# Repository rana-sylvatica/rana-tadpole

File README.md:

# rana-tadpole
## Pocket-sized digital controller

### Overview:

#### NOTE: I am in the process of updating this repository with information and design files for the Rana Tadpole V2.  This process isn't quite done yet - wait a few days if you are looking to build your own Tadpole V2 (I'll remove this note once I'm done with the update).  The V2 motherboard files are now up, I'll be getting to adding the case file and other stuff Soon(TM)

The Rana Tadpole is a pocket-sized 20-button digital controller, designed for platform fighters but usable for other fighting games, platformers, etc.

Unlike most other similar controller designs that use either keyboard switches or arcade buttons, the Tadpole uses mouse switches (Kailh GM 4.0 if using the provided BOM files - there are other compatible switches that can be subsituted as well at the builders discretion).

With the mouseclick switches, the Tadpole has best-in-class button travel distance, a mere 0.8mm until bottom-out, for fast reactions and precise inputs.  The mouseclick switches also enable the entire board to be easily factory assembled, cutting down on cost and build time.

This repository contains design files for all required components to build your own Rana Tadpole.  Scroll down for open source license information, parts list, link to build guide, and user guide.

### Attributions:

Many thanks to [Quark](https://github.com/Armastardo) for the PCB design for both the motherboard and daughterboard!

### Licensing:

This project is licensed under CERN Open Hardware Licence Version 2 - Strongly Reciprocal

In short, this means:
 - License applies to publicly available hardware designs
 - Allows use, reproduction, modification, distribution, and sale of the design
 - License requires distribution under same terms, attribution to original designer(s)
 - Does not grant trademark rights, includes disclaimer of liability
 - License may be terminated for non-compliance

Anyone may use these design files to make their own Rana Tadpole(s) for personal use or to sell, or modify the design however they wish.
However, if a modified design is distributed (either digitally or physically beyond personal use), the modified design must be publicly posted under the same terms.

Note: if selling Rana Tadpoles, YOU MUST link to this repo (or your fork of this repo, if you modify the design) on your store page.  If selling in-person, MAKE SURE to communicate that this is an open-source project, and provide (via QR code or similar) a way for the customer to access this repo (or the applicable fork).

All these files are posted as-is. This source is distributed WITHOUT ANY EXPRESS OR IMPLIED WARRANTY, INCLUDING OF MERCHANTABILITY, SATISFACTORY QUALITY AND FITNESS FOR A PARTICULAR PURPOSE. 

If you are interested in supporting this project, donations are accepted at [paypal.me/RanaLabs](https://www.paypal.me/RanaLabs).

### Rana Tadpole V2 Animation

https://github.com/user-attachments/assets/85642930-a598-4af2-86c9-3ccd63989db8

### Parts list:

The Rana Tadpole build requires the following list of components:
 - #### Case
   - 3D printed or CNC machined, see CAD files
   - Additional notes:
     - JLCPCB or PCBway are affordable CNC machining vendors.  If you want the screw holes threaded at the factory (rather than doing it by hand), you will need to create a drawing specifying the thread type, hole position, and thread depth.
     - If 3D printing the case, the provided file is designed to have the screws thread directly into the plastic.  Getting a good fit on your printer may require some adjustment.  The files can also be modified to accept heat set inserts, or other screws (such as specialized thread-cutting screws) can be subsituted for the machine screws as well.  Just do your research on hole diameters, etc.
     - I plan to post a case model in the future that is designed for ordering inexpensively from a 3D printing service such as JLCPCB, but that design is not quite ready yet.
 - #### Button caps
   - These can be purchased from me (injection molded PBT) or 3D printed.  Link to purchase: https://ko-fi.com/s/469357a31c
   - Additional notes for 3D printing:
     - For best quality, order the Tadpole_Button_x8 file from JLCPCB or other 3D printing service in SLS or MJF nylon
     - Resin printing also works well
     - These buttons are difficult to print with a FDM printer, but please let me know if you find a modification to the design that allows them to print well!
 - #### Motherboard
   - Embedded rp2040 PCB with factory-soldered mouseclick switches, see KiCAD and Gerber files
   - The Gerber and assembly files are generated for ordering through JLCPCB.  Other PCB fabs can also be used, but you may need to generate the production files differently.  (applicable to all three PCB components here)
 - #### USB Breakout board
   - USB C board with case grounding and ESD protection, see KiCAD and Gerber files
 - #### Backplate
   - Silkscreen PCB (or lasercut/3D printed). KiCAD/Gerber, DXF, and .STEP files available
 - #### Foam pads
   - These can be purchased from me (die cut textured silicone rubber), or lasercut from EVA foam or similar.  Link to purcahse from me: https://ko-fi.com/s/3146277fc0
   - Example foam that works well: https://www.amazon.com/gp/product/B07V5PR459
 - ####  Ribbon cable
   - 12 pin, 0.5mm pitch, 50mm length FFC, Same side contacts (sometimes called "Forward Direction"
   - Example items: https://www.digikey.com/en/products/detail/assmann-wsw-components/AFFC-050-12-051-11/6570261, [https://www.aliexpress.us/item/3256803954097404.html](https://www.aliexpress.us/item/3256805295157150.html)
 - #### Grounding foam
   - Optional, but helps with ESD protection if using the PCB backplate.  Link: https://www.aliexpress.us/item/3256805239781097.html 
 - #### Hardware
   - Screws
     - 2x M3x6mm (for securing the USB C board).  Link: https://www.mcmaster.com/94500A221/
     - 6x M3x10mm (for securing the backplate/motherboard).  Link: [https://www.mcmaster.com/92095A181/](https://www.mcmaster.com/92095A182/) OR [https://www.aliexpress.us/item/2255800885711092.html](https://www.aliexpress.us/item/3256804883804669.html?)
   - Spacers
     - Can either use:
       - 6x X-profile o-rings, dash number 104.  Link: https://www.mcmaster.com/90025K513/
       - 3mm thick gaskets using the files in this repo - these can be 3D printed in soft TPU or die cut from silicone or similar

#### Extras: 
 - #### USB C-USB A cable (for PC/switch compatibility)
   - Any USB data cable will work
 - #### USB C-GCC cable (for gamecube/wii compatibility)
   - Several suppliers, but HHL or my store are good options: https://handheldlegend.com/products/retro-c-gamecube-cable-usb-c-to-gamecube-cable?variant=40183052337286, https://ko-fi.com/s/bc4af1084a
 - #### Belt clip
   - .STL file provided for 3D printing
 - #### Carry bag
   - Canvas zipper pouches that measure at least 8" x 6" work well

### Assembly guide:

See YouTube video: https://www.youtube.com/watch?v=oF4wL67agoM

NOTE: This is slightly out of date now, given the V2 version that adds the slide switch.  I may eventually make an updated build guide, but for now this is still mostly relevant.

### Dual Firmware Switch:

The Rana Tadpole V2 has a fun new feature - two different flash memory chips, with a switch on the side of the controller to select between them.  This is very useful if you want to use your Tadpole for both platform fighters and traditional fighters - you can load HayBox on one memory slot and GP2040-CE on the other.

#### IMPORTANT NOTE: Do not flip the firmware switch while the device is plugged in.  Unplug it, flip the switch to the other position, and plug it back in.

### Aux USB C Port:

Another new feature of the Tadpole V2 is the auxillary USB C port on the side of the controller.  The main purpose of this is for passthrough authentication when using GP2040-CE firmware, to get PS4/PS5 compatibility without additional input latency (see image below).

This port is also capable of becoming a flexible expansion port in the future, with many possibilities including: an adapter to connect a GCC for mixed input (left hand GCC, right hand Tadpole) gameplay, pluggable analog joystick(s), etc.

#### MORE INFO TO COME HERE

### Firmwares:

There are three different open-source firmwares that the Rana Tadpole is compatible with: 
 - [HayBox](https://github.com/JonnyHaystack/HayBox)
   - Compatible with:
     - PC (as XInput or DInput device)
     - GameCube
     - Wii
     - Switch
     - N64
     - Other consoles (via Brook Wingman adapter)
 - [pico-rectangle](https://github.com/JulienBernard3383279/pico-rectangle)
   - Compatible with:
     - PC (as emulated GC adapter or XInput device)
     - GameCube
     - Wii
     - Switch
     - Other consoles (via Brook Wingman adapter)
 - [GP2040-CE](https://gp2040-ce.info/#/README)
   - Generally used for traditional fighting games, compatible with:
     - PC
     - PS3
     - PS4
     - Switch
     - Other consoles (via Brook Wingman adapter)
    
    Please refer to the documentation for each firmware for more information.

   #### Default layouts:

   HayBox and pico-rectangle:

   GP2040-CE:

   #### Switching and flashing firmwares:

   To flash a firmware, the rp2040 chip inside the Tadpole motherboard must be put in BOOTSEL mode, at which point the controller will show up as a mass storage device when plugged into a computer and the fimrware file can be copied to it.

   There are two ways of putting the Tadpole in BOOTSEL mode.  First, there is a small button on the motherboard that can be held down as the board is plugged into the PC.  However, this can be inconvenient as it requires disassembling the controller to access this button.

   The alternative method is to use hold a button (or button combination) specific to the particular firmware, when plugging into the PC.
   - For HayBox: hold Start (may be different if using a fork of HayBox.  For example, https://github.com/GRAMCTRL/HayBox-GRAM uses "A" as the button hold to get into BOOTSEL mode).
   - For pico-rectangle: hold C-Right
   - For GP2040-CE: hold Start + Select + Up (refer to the GP2040-CE layout graphic)
  
   Additional notes on HayBox:
   - The HayBox-GRAM fork brings a few features such as web remapping (see below) and a dedicated Rivals 2 mode, that aren't (yet) in a pre-compiled release of mainline HayBox.
     - In the firmware-binaries folder is a .UF2 file for the Tadpole configuration of this firmware.  Until there is a mainline HayBox release that includes these new features, this is a good choice.
     - To access the remapper, go to remapp.ing, hold Start when plugging in the Tadpole, and follow the instructions on the screen.
  
   Additional notes on GP2040-CE:
   - The Rana Tadpole version of GP2040-CE can be downloaded from: https://gp2040-ce.info/downloads (scroll down until you find the Tadpole download link)
   - Hold Start (refer to the GP2040-CE layout graphic) on plugin to put it in web-config mode to change button mappings, go to https://gp2040-ce.info/web-configurator/ to access the configurator
   - To enable passthrough authentication for PS4/PS5 compatibility (with an appropriate adapter such as a Brook Wingman, Honson F5, Mayflash Magicboots, or Haute42 Booter5), go to the peripheral mapping section of the GP2040-CE Web Configurator and enable USB Host  mode on pin 9 as shown in the image below:

### Support
 
   The easiest way to get in touch with me or other Tadpole users is the Rana Labs Discord Server: https://discord.gg/9wBaMWgJkv

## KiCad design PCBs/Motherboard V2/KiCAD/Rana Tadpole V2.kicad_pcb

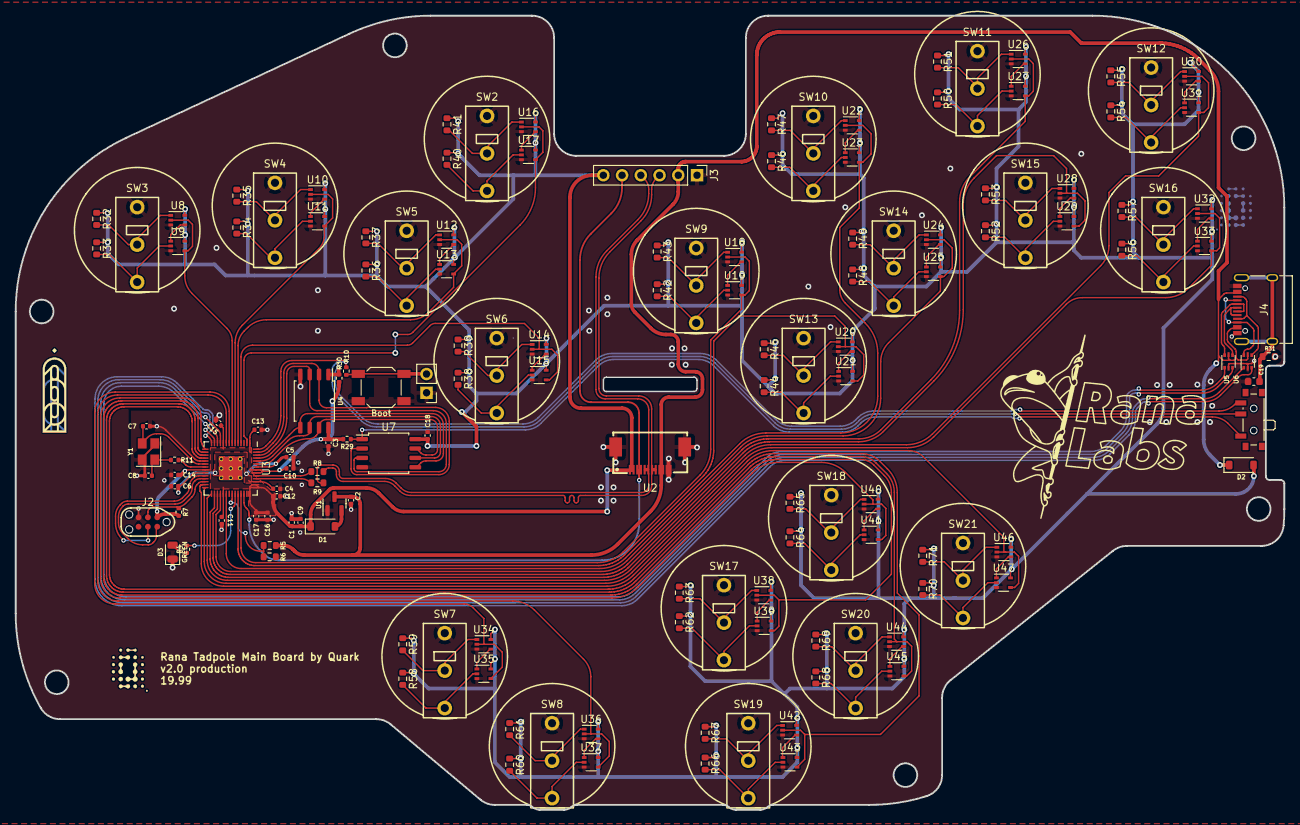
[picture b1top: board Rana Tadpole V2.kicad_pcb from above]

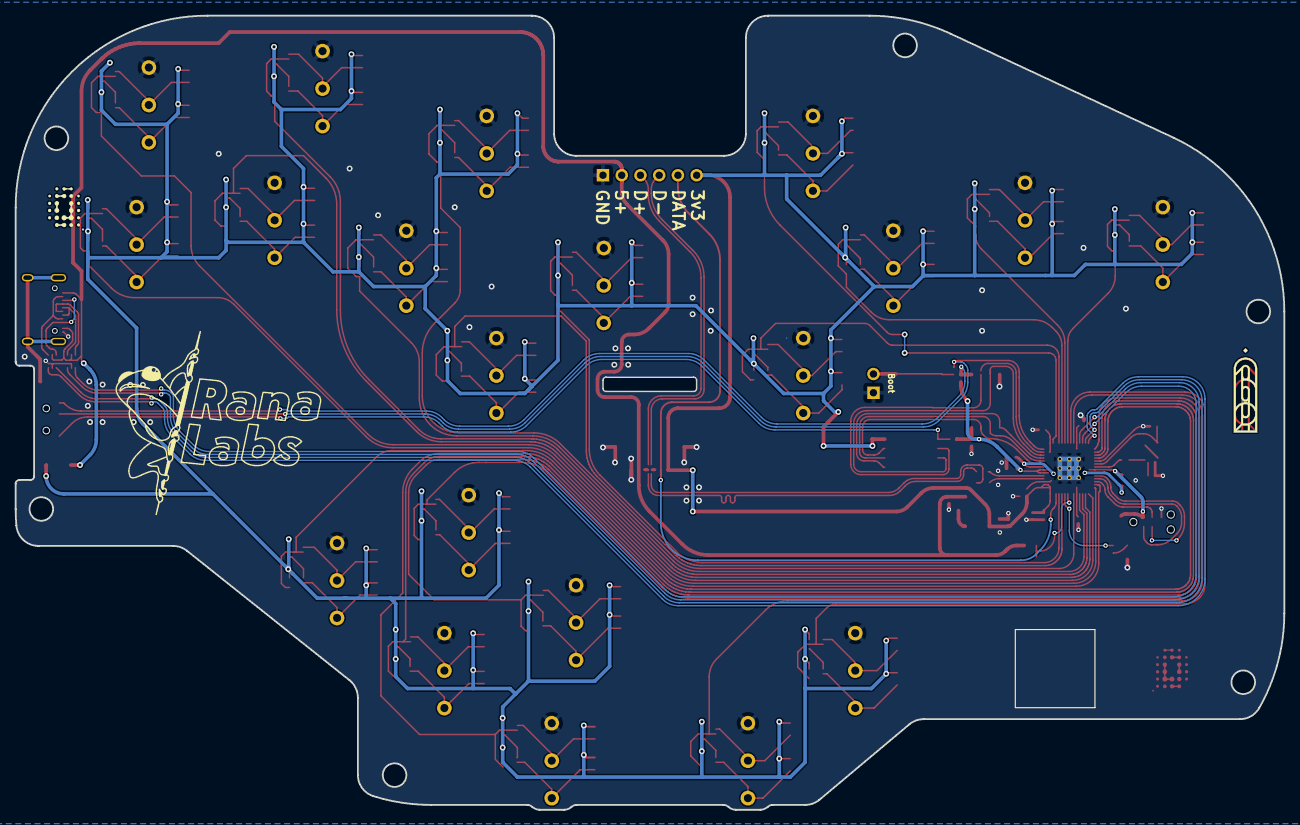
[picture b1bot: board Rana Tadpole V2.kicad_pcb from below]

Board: 2 copper layers, 172.0 x 107.7 mm, 151 parts (2 on the bottom side), 117 nets.

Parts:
C1, C2, C4, C10: 1uF; C_0402_1005Metric
C3, C5, C6, C11, C12, C13, C14, C15, C16, C17, C18: 100nF; C_0402_1005Metric
C7, C8: 22pF; C_0402_1005Metric
C9: 10uF; C_0402_1005Metric
C19: 4.7u; C_0603_1608Metric
D1, D2: Schottky Diode; D_SOD-123
D3: GREEN; LED_0805_2012Metric
H1, H3: qw-logo; qw new logo silk + copper sm
H2, H4: 19.99 logo; 1999 logo md
J1: Conn_01x02; PinHeader_1x02_P2.54mm_Vertical
J2: JTAG_TC2030; CON_TC2030_outlined
J3: DuPont Connector; PinHeader_1x06_P2.54mm_Vertical
J4: USB_C_Receptacle_USB2.0; USB_C_Receptacle_XKB_U262-16XN-4BVC11
R4: 470; R_0402_1005Metric
R5: 5.6k; R_0603_1608Metric
R6, R32, R35, R37, R39, R41, R43, R45, R47, R49, R51, R53, R55, R57, R59, R61, R63, R65, R67, R69, R71: 10k; R_0603_1608Metric
R7, R29, R30: 10k; R_0402_1005Metric
R8, R9: 27; R_0603_1608Metric
R10, R11: 1k; R_0402_1005Metric
R31: 1M; R_0603_1608Metric
R33, R34, R36, R38, R40, R42, R44, R46, R48, R50, R52, R54, R56, R58, R60, R62, R64, R66, R68, R70: 10K; R_0603_1608Metric
SW1: Boot; SW_SPST_SKQG_WithStem
SW2, SW3, SW4, SW5, SW6, SW7, SW8, SW9, SW10, SW11, SW12, SW13, SW14, SW15, SW16, SW17, SW18, SW19, SW20, SW21: RanaTadpole
SW22: SW_SPDT; SW_SPDT_PCM12
U1: XC6206; SOT-23
U2: X05A26H12G; FPC-SMD_X05A26H12G
U3: RP2040; RP2040-QFN-56
U4, U7: W25Q128JVS; SOIC-8_5.23x5.23mm_P1.27mm
U5, U6: USBLC6-2P6; SOT-666
U8, U9, U10, U11, U12, U13, U14, U15, U16, U17, U18, U19, U20, U21, U22, U23, U24, U25, U26, U27, U28, U29, U30, U31, U32, U33, U34, U35, U36, U37, U38, U39, U40, U41, U42, U43, U44, U45, U46, U47: 74LVC1G00; SOT-353_SC-70-5
Y1: 12MHz; Crystal_SMD_3225-4Pin_3.2x2.5mm

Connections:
3vDiode: C1.2, C3.1, C9.1, C10.1, C11.1, C12.1, C13.1, C14.1, C15.1, C16.1, C17.1, C18.1, D1.1 (K), D2.2 (A), J2.1 (VCC), J3.6, R7.1, R29.1, R30.1, R32.1, R33.1, R34.1, R35.1, R36.1, R37.1, R38.1, R39.1, R40.1, R41.1, R42.1, R43.1, R44.1, R45.1, R46.1, R47.1, R48.1, R49.1, R50.1, R51.1, R52.1, R53.1, R54.1, R55.1, R56.1, R57.1, R58.1, R59.1, R60.1, R61.1, R62.1, R63.1, R64.1, R65.1, R66.1, R67.1, R68.1, R69.1, R70.1, R71.1, U2.1, U2.2, U3.1 (IOVDD), U3.10 (IOVDD), U3.22 (IOVDD), U3.33 (IOVDD), U3.42 (IOVDD), U3.43 (ADC_AVDD), U3.44 (VREG_VIN), U3.48 (USB_VDD), U3.49 (IOVDD), U4.8 (VCC), U7.8 (VCC), U8.5 (VCC), U9.5 (VCC), U10.5 (VCC), U11.5 (VCC), U12.5 (VCC), U13.5 (VCC), U14.5 (VCC), U15.5 (VCC), U16.5 (VCC), U17.5 (VCC), U18.5 (VCC), U19.5 (VCC), U20.5 (VCC), U21.5 (VCC), U22.5 (VCC), U23.5 (VCC), U24.5 (VCC), U25.5 (VCC), U26.5 (VCC), U27.5 (VCC), U28.5 (VCC), U29.5 (VCC), U30.5 (VCC), U31.5 (VCC), U32.5 (VCC), U33.5 (VCC), U34.5 (VCC), U35.5 (VCC), U36.5 (VCC), U37.5 (VCC), U38.5 (VCC), U39.5 (VCC), U40.5 (VCC), U41.5 (VCC), U42.5 (VCC), U43.5 (VCC), U44.5 (VCC), U45.5 (VCC), U46.5 (VCC), U47.5 (VCC)
+1V1: C4.1, C5.1, C6.1, U3.23 (DVDD), U3.45 (VREG_VOUT), U3.50 (DVDD)
/D_+: R8.2, U3.47 (D+)
/D_-: R9.2, U3.46 (D-)
/XTAL_O: C8.2, R11.1, Y1.1
/~USB_BOOT: J1.2, R10.1, SW1.2
A: U3.17 (GPIO14), U44.2, U45.4
AUX_USB_D+: J4.A6 (D+), J4.B6 (D+), U5.6 (I/O1)
AUX_USB_D+_PRTC: U3.12 (GPIO9), U5.1 (I/O1)
AUX_USB_D-: J4.A7 (D-), J4.B7 (D-), U5.4 (I/O2)
AUX_USB_D-_PRTC: U3.11 (GPIO8), U5.3 (I/O2)
AUX_USB_VBUS: C2.2, D2.1 (K), J3.2, J4.A4 (VBUS), J4.A9 (VBUS), J4.B4 (VBUS), J4.B9 (VBUS), R5.1, U1.3 (VI), U2.9, U2.10, U5.5 (VBUS), U6.5 (VBUS)
B: U3.38 (GPIO26/ADC0), U20.2, U21.4
CS: R10.2, SW22.2 (B), U3.56 (QSPI_SS_N)
C_DN: U3.18 (GPIO15), U42.2, U43.4
C_LT: U3.16 (GPIO13), U38.2, U39.4
C_RT: U3.27 (GPIO16), U46.2, U47.4
C_UP: U3.15 (GPIO12), U40.2, U41.4
D+: J3.3, R8.1, U2.7, U2.8
D-: J3.4, R9.1, U2.5, U2.6
DATA: J3.5, U2.3, U2.4, U3.40 (GPIO28/ADC2)
DOWN: U3.5 (GPIO3), U12.2, U13.4
EXTRA_GPIO: J4.A8 (SBU1), J4.B8 (SBU2), U6.6 (I/O1)
EXTRA_GPIO_PRTC: U3.13 (GPIO10), U6.1 (I/O1)
GCC_DATA_IN: J4.A5 (CC1), J4.B5 (CC2), U6.4 (I/O2)
GCC_DATA_IN_PRTC: U3.14 (GPIO11), U6.3 (I/O2)
GND: C1.1, C2.1, C3.2, C4.2, C5.2, C6.2, C7.1, C8.1, C9.2, C10.2, C11.2, C12.2, C13.2, C14.2, C15.2, C16.2, C17.2, C18.2, C19.1, D3.1 (K), J1.1, J2.5 (GND), J3.1, J4.A1 (GND), J4.A12 (GND), J4.B1 (GND), J4.B12 (GND), R6.2, R31.1, SW1.1, SW2.1, SW3.1, SW4.1, SW5.1, SW6.1, SW7.1, SW8.1, SW9.1, SW10.1, SW11.1, SW12.1, SW13.1, SW14.1, SW15.1, SW16.1, SW17.1, SW18.1, SW19.1, SW20.1, SW21.1, U1.1 (GND), U2.11, U2.12, U2.13, U2.14, U3.19 (TESTEN), U3.57 (GND), U4.4 (GND), U5.2 (GND), U6.2 (GND), U7.4 (GND), U8.3 (GND), U9.3 (GND), U10.3 (GND), U11.3 (GND), U12.3 (GND), U13.3 (GND), U14.3 (GND), U15.3 (GND), U16.3 (GND), U17.3 (GND), U18.3 (GND), U19.3 (GND), U20.3 (GND), U21.3 (GND), U22.3 (GND), U23.3 (GND), U24.3 (GND), U25.3 (GND), U26.3 (GND), U27.3 (GND), U28.3 (GND), U29.3 (GND), U30.3 (GND), U31.3 (GND), U32.3 (GND), U33.3 (GND), U34.3 (GND), U35.3 (GND), U36.3 (GND), U37.3 (GND), U38.3 (GND), U39.3 (GND), U40.3 (GND), U41.3 (GND), U42.3 (GND), U43.3 (GND), U44.3 (GND), U45.3 (GND), U46.3 (GND), U47.3 (GND), Y1.2, Y1.4
L: U3.7 (GPIO5), U8.2, U9.4
LEFT: U3.6 (GPIO4), U10.2, U11.4
LS: U3.31 (GPIO20), U26.2, U27.4
M1: U3.8 (GPIO6), U34.2, U35.4
M2: U3.9 (GPIO7), U36.2, U37.4
MB1: R29.2, SW22.1 (A), U7.1 (~CS)
MB2: R30.2, SW22.3 (C), U4.1 (~CS)
MS: U3.29 (GPIO18), U30.2, U31.4
unnamed: D1.2 (A), U1.2 (VO)
unnamed: D3.2 (A), R4.2
unnamed: C19.2, J4.S1 (SHIELD), R31.2
unnamed: R32.2, SW3.2, U8.1
unnamed: R33.2, SW3.3, U9.2
unnamed: R34.2, SW4.3, U11.2
unnamed: R35.2, SW4.2, U10.1
unnamed: R36.2, SW5.3, U13.2
unnamed: R37.2, SW5.2, U12.1
unnamed: R38.2, SW6.3, U15.2
unnamed: R39.2, SW6.2, U14.1
unnamed: R40.2, SW2.3, U17.2
unnamed: R41.2, SW2.2, U16.1
unnamed: R42.2, SW9.3, U19.2
unnamed: R43.2, SW9.2, U18.1
unnamed: R44.2, SW13.3, U21.2
unnamed: R45.2, SW13.2, U20.1
unnamed: R46.2, SW10.3, U23.2
unnamed: R47.2, SW10.2, U22.1
unnamed: R48.2, SW14.3, U25.2
unnamed: R49.2, SW14.2, U24.1
unnamed: R50.2, SW11.3, U27.2
unnamed: R51.2, SW11.2, U26.1
unnamed: R52.2, SW15.3, U29.2
unnamed: R53.2, SW15.2, U28.1
unnamed: R54.2, SW12.3, U31.2
unnamed: R55.2, SW12.2, U30.1
unnamed: R56.2, SW16.3, U33.2
unnamed: R57.2, SW16.2, U32.1
unnamed: R58.2, SW7.3, U35.2
unnamed: R59.2, SW7.2, U34.1
unnamed: R60.2, SW8.3, U37.2
unnamed: R61.2, SW8.2, U36.1
unnamed: R62.2, SW17.3, U39.2
unnamed: R63.2, SW17.2, U38.1
unnamed: R64.2, SW18.3, U41.2
unnamed: R65.2, SW18.2, U40.1
unnamed: R66.2, SW19.3, U43.2
unnamed: R67.2, SW19.2, U42.1
unnamed: R68.2, SW20.3, U45.2
unnamed: R69.2, SW20.2, U44.1
unnamed: R70.2, SW21.3, U47.2
unnamed: R71.2, SW21.2, U46.1
unnamed: U8.4, U9.1
unnamed: U10.4, U11.1
unnamed: U12.4, U13.1
unnamed: U14.4, U15.1
unnamed: U16.4, U17.1
unnamed: U18.4, U19.1
unnamed: U20.4, U21.1
unnamed: U22.4, U23.1
unnamed: U24.4, U25.1
unnamed: U26.4, U27.1
unnamed: U28.4, U29.1
unnamed: U30.4, U31.1
unnamed: U32.4, U33.1
unnamed: U34.4, U35.1
unnamed: U36.4, U37.1
unnamed: U38.4, U39.1
unnamed: U40.4, U41.1
unnamed: U42.4, U43.1
unnamed: U44.4, U45.1
unnamed: U46.4, U47.1
PICO_LED: R4.1, U3.37 (GPIO25)
QSPI_CLK: U3.52 (QSPI_SCLK), U4.6 (CLK), U7.6 (CLK)
R: U3.39 (GPIO27/ADC1), U18.2, U19.4
RIGHT: U3.4 (GPIO2), U14.2, U15.4
SD0: U3.53 (QSPI_SD0), U4.5 (DI(IO0)), U7.5 (DI(IO0))
SD1: U3.55 (QSPI_SD1), U4.2 (DO(IO1)), U7.2 (DO(IO1))
SD2: U3.54 (QSPI_SD2), U4.3 (IO2), U7.3 (IO2)
SD3: U3.51 (QSPI_SD3), U4.7 (IO3), U7.7 (IO3)
START: U3.2 (GPIO0), U16.2, U17.4
SWCLK: J2.4 (SWCLK), U3.24 (SWCLK)
SWD: J2.2 (SWDIO), U3.25 (SWDIO)
UP: U3.28 (GPIO17), U32.2, U33.4
VBUS_SENSE: R5.2, R6.1, U3.36 (GPIO24)
X: U3.32 (GPIO21), U24.2, U25.4
XTAL_IN: C7.2, U3.20 (XTAL_IN), Y1.3
XTAL_OUT: R11.2, U3.21 (XTAL_OUT)
Y: U3.34 (GPIO22), U22.2, U23.4
Z: U3.30 (GPIO19), U28.2, U29.4
~RESET: J2.3 (~RST), R7.2, U3.26 (~RUN)

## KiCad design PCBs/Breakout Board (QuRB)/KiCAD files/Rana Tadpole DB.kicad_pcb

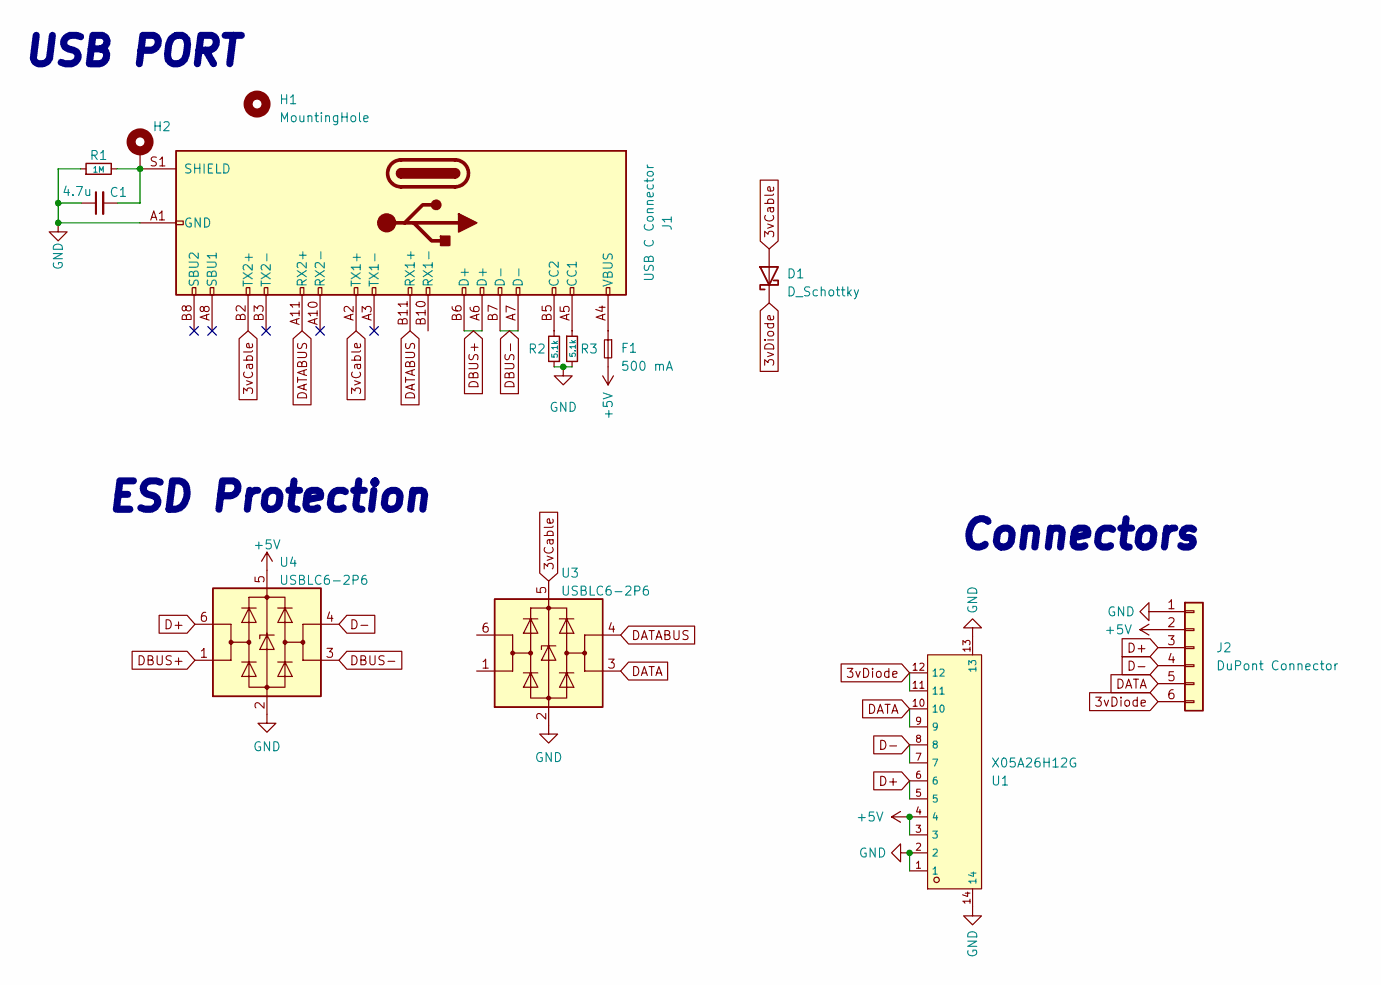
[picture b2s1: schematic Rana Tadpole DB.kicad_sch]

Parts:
C1: 4.7u; C_0603_1608Metric; LCSC C19666
D1: D_Schottky; D_SOD-323; LCSC C191023
F1: 500 mA; Fuse_0603_1608Metric; LCSC C883095
H1: MountingHole; MountingHole_3.2mm_M3_DIN965_Pad
H2: MountingHole_Pad; MountingHole_3.2mm_M3_DIN965_Pad
J1: USB C Connector; TYPE-C_24P_QCHT; LCSC C456013
J2: DuPont Connector; PinHeader_1x06_P2.54mm_Vertical
R1: 1M; R_0603_1608Metric; LCSC C25190
R2, R3: 5.1k; R_0603_1608Metric; LCSC C23186
U1: X05A26H12G; FPC-SMD_X05A26H12G; LCSC C519263
U3, U4: USBLC6-2P6; SOT-666; LCSC C2827693

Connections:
3vCable: D1.2 (A), J1.A2 (TX1+), J1.B2 (TX2+), U3.5 (VBUS)
3vDiode: D1.1 (K), J2.6, U1.11, U1.12
+5V: F1.2, J2.2, U1.3, U1.4, U4.5 (VBUS)
D+: J2.3, U1.5, U1.6, U4.6 (I/O1)
D-: J2.4, U1.7, U1.8, U4.4 (I/O2)
DATA: J2.5, U1.9, U1.10, U3.3 (I/O2)
DATABUS: J1.A11 (RX2+), J1.B11 (RX1+), U3.4 (I/O2)
DBUS+: J1.A6 (D+), J1.B6 (D+), U4.1 (I/O1)
DBUS-: J1.A7 (D-), J1.B7 (D-), U4.3 (I/O2)
GND: C1.1, J1.A1 (GND), J1.A12 (GND), J1.B1 (GND), J1.B12 (GND), J2.1, R1.1, R2.1, R3.2, U1.1, U1.2, U1.13, U1.14, U3.2 (GND), U4.2 (GND)
unnamed: F1.1, J1.A4 (VBUS), J1.A9 (VBUS), J1.B4 (VBUS), J1.B9 (VBUS)
unnamed: J1.A5 (CC1), R3.1
unnamed: J1.B5 (CC2), R2.2
unnamed: C1.2, H2.1, J1.S1 (SHIELD), R1.2

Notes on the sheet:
ESD Protection
Connectors
USB PORT

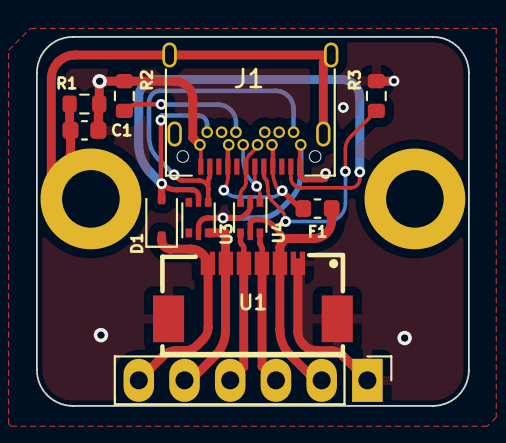
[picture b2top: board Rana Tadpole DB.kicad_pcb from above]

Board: 2 copper layers, 24.0 x 20.5 mm, 13 parts (0 on the bottom side), 14 nets.

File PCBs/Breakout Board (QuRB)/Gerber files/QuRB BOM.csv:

Designator,Footprint,Quantity,Value,LCSC Part #
C1,0603,1,4.7u,C19666
D1,D_SOD-323,1,D_Schottky,C191023
F1,0603,1,500 mA,C883095
J1,TYPE-C_24P_QCHT,1,USB C Connector,C456013
R1,0603,1,1M,C25190
"R2, R3",0603,2,5.1k,C23186
U1,FPC-SMD_X05A26H12G,1,X05A26H12G,C519263
"U3, U4",SOT-666,2,USBLC6-2P6,C2827693

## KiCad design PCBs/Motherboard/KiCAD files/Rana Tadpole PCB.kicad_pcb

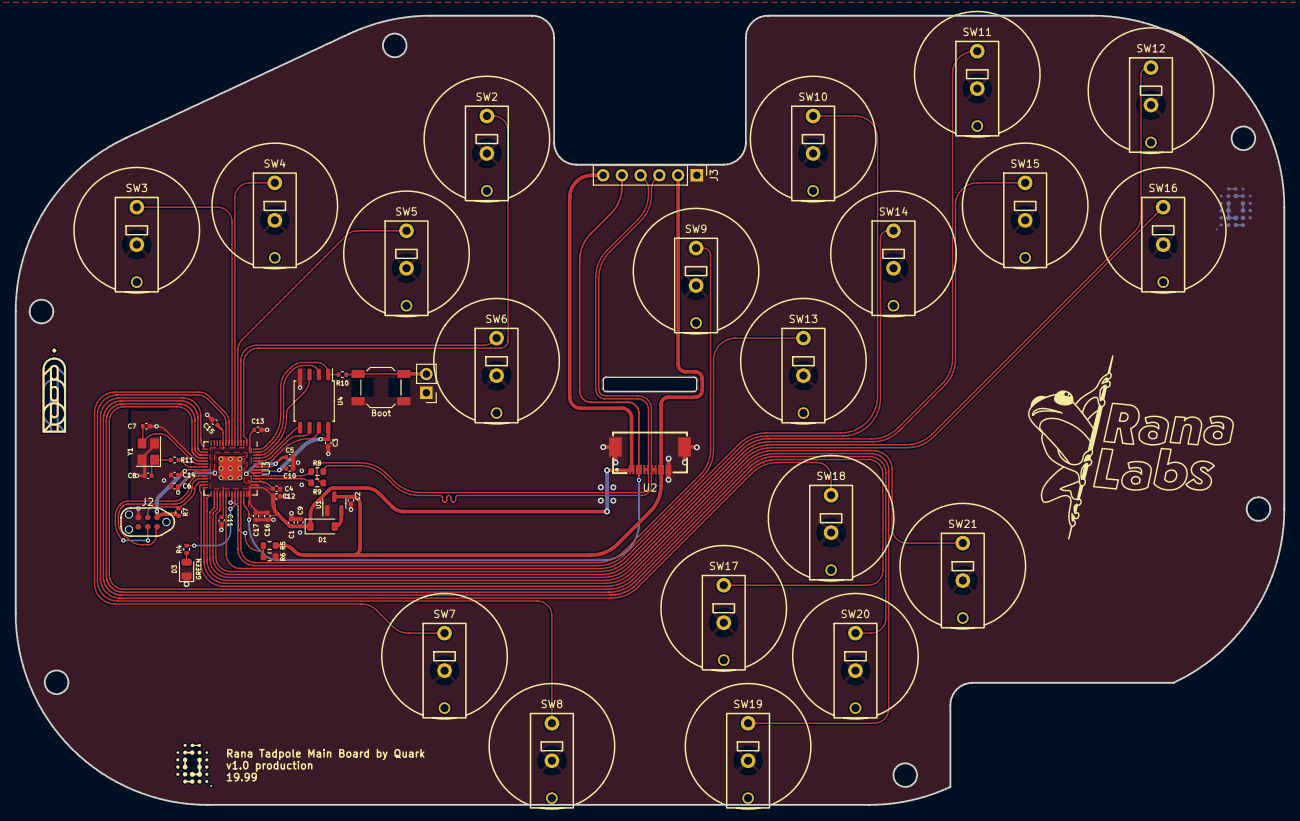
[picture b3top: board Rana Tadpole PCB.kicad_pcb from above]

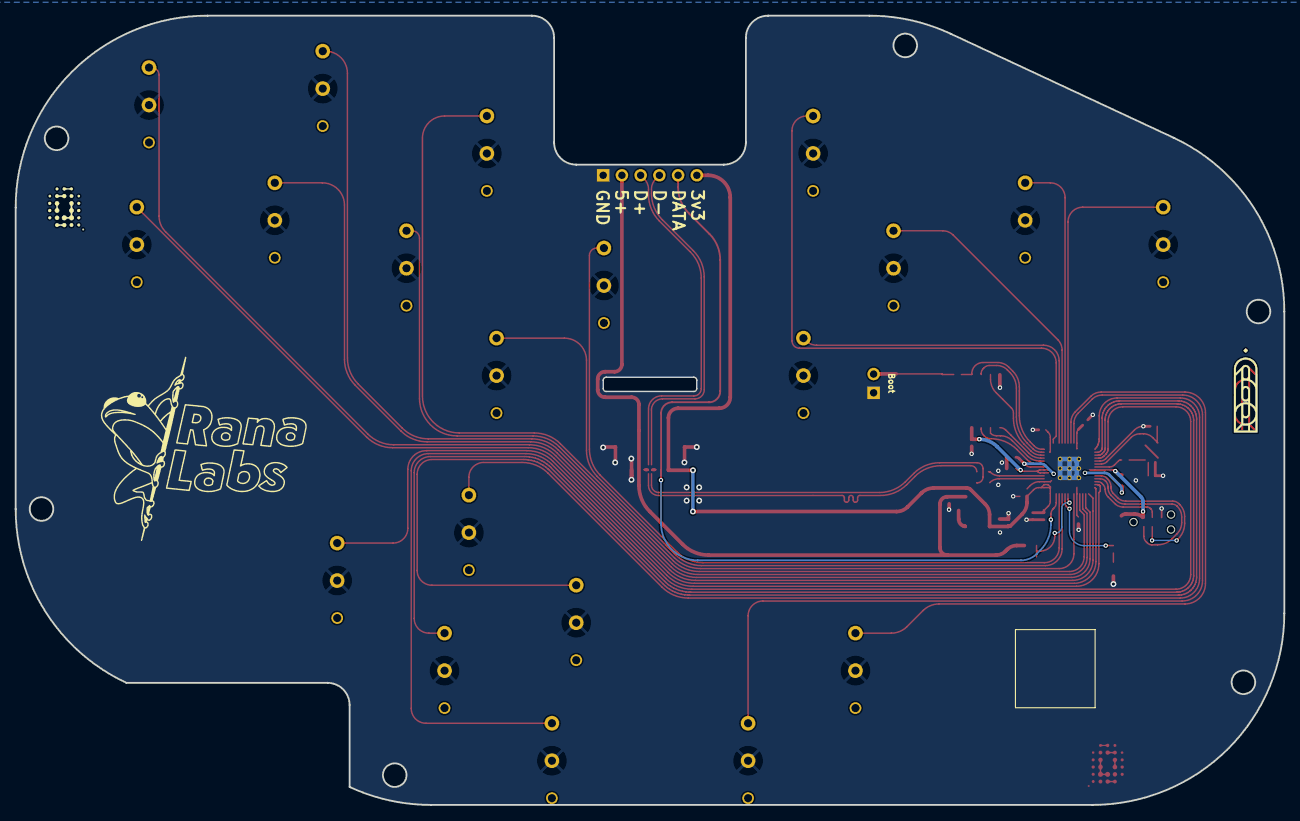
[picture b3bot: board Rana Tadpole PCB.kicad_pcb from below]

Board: 2 copper layers, 172.0 x 107.0 mm, 60 parts (2 on the bottom side), 46 nets.

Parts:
C1, C2, C4, C10: 1uF; C_0402_1005Metric
C3, C5, C6, C11, C12, C13, C14, C15, C16, C17: 100nF; C_0402_1005Metric
C7, C8: 22pF; C_0402_1005Metric
C9: 10uF; C_0402_1005Metric
D1: Schottky Diode; D_SOD-123
D3: GREEN; LED_0805_2012Metric
H1, H3: qw-logo; qw new logo silk + copper sm
H2, H4: 19.99 logo; 1999 logo md
J1: Conn_01x02; PinHeader_1x02_P2.54mm_Vertical
J2: JTAG_TC2030; CON_TC2030_outlined
J3: DuPont Connector; PinHeader_1x06_P2.54mm_Vertical
R4: 470; R_0402_1005Metric
R5: 5.6k; R_0603_1608Metric
R6: 10k; R_0603_1608Metric
R7: 10k; R_0402_1005Metric
R8, R9: 27; R_0603_1608Metric
R10, R11: 1k; R_0402_1005Metric
SW1: Boot; SW_SPST_SKQG_WithStem
SW2, SW3, SW4, SW5, SW6, SW7, SW8, SW9, SW10, SW11, SW12, SW13, SW14, SW15, SW16, SW17, SW18, SW19, SW20, SW21: RanaTadpole
U1: XC6206; SOT-23
U2: X05A26H12G; FPC-SMD_X05A26H12G
U3: RP2040; RP2040-QFN-56
U4: W25Q128JVS; SOIC-8_5.23x5.23mm_P1.27mm
Y1: 12MHz; Crystal_SMD_3225-4Pin_3.2x2.5mm

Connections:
3vDiode: C1.2, C3.1, C9.1, C10.1, C11.1, C12.1, C13.1, C14.1, C15.1, C16.1, C17.1, D1.1 (K), J2.1 (VCC), J3.6, R7.1, U2.1, U2.2, U3.1 (IOVDD), U3.10 (IOVDD), U3.22 (IOVDD), U3.33 (IOVDD), U3.42 (IOVDD), U3.43 (ADC_AVDD), U3.44 (VREG_VIN), U3.48 (USB_VDD), U3.49 (IOVDD), U4.8 (VCC)
+1V1: C4.1, C5.1, C6.1, U3.23 (DVDD), U3.45 (VREG_VOUT), U3.50 (DVDD)
+5V: C2.2, J3.2, R5.1, U1.3 (VI), U2.9, U2.10
/D_+: R8.2, U3.47 (D+)
/D_-: R9.2, U3.46 (D-)
/XTAL_O: C8.2, R11.1, Y1.1
/~USB_BOOT: J1.2, R10.1, SW1.2
A: SW20.1, U3.17 (GPIO14)
B: SW13.1, U3.38 (GPIO26/ADC0)
CS: R10.2, U3.56 (QSPI_SS_N), U4.1 (~CS)
C_DN: SW19.1, U3.18 (GPIO15)
C_LT: SW17.1, U3.16 (GPIO13)
C_RT: SW21.1, U3.27 (GPIO16)
C_UP: SW18.1, U3.15 (GPIO12)
D+: J3.3, R8.1, U2.7, U2.8
D-: J3.4, R9.1, U2.5, U2.6
DATA: J3.5, U2.3, U2.4, U3.40 (GPIO28/ADC2)
DOWN: SW5.1, U3.5 (GPIO3)
GND: C1.1, C2.1, C3.2, C4.2, C5.2, C6.2, C7.1, C8.1, C9.2, C10.2, C11.2, C12.2, C13.2, C14.2, C15.2, C16.2, C17.2, D3.1 (K), J1.1, J2.5 (GND), J3.1, R6.2, SW1.1, SW2.2, SW3.2, SW4.2, SW5.2, SW6.2, SW7.2, SW8.2, SW9.2, SW10.2, SW11.2, SW12.2, SW13.2, SW14.2, SW15.2, SW16.2, SW17.2, SW18.2, SW19.2, SW20.2, SW21.2, U1.1 (GND), U2.11, U2.12, U2.13, U2.14, U3.19 (TESTEN), U3.57 (GND), U4.4 (GND), Y1.2, Y1.4
L: SW3.1, U3.7 (GPIO5)
LEFT: SW4.1, U3.6 (GPIO4)
LS: SW11.1, U3.31 (GPIO20)
M1: SW7.1, U3.8 (GPIO6)
M2: SW8.1, U3.9 (GPIO7)
MS: SW12.1, U3.29 (GPIO18)
unnamed: D1.2 (A), U1.2 (VO)
unnamed: D3.2 (A), R4.2
PICO_LED: R4.1, U3.37 (GPIO25)
QSPI_CLK: U3.52 (QSPI_SCLK), U4.6 (CLK)
R: SW9.1, U3.39 (GPIO27/ADC1)
RIGHT: SW6.1, U3.4 (GPIO2)
SD0: U3.53 (QSPI_SD0), U4.5 (DI(IO0))
SD1: U3.55 (QSPI_SD1), U4.2 (DO(IO1))
SD2: U3.54 (QSPI_SD2), U4.3 (IO2)
SD3: U3.51 (QSPI_SD3), U4.7 (IO3)
START: SW2.1, U3.2 (GPIO0)
SWCLK: J2.4 (SWCLK), U3.24 (SWCLK)
SWD: J2.2 (SWDIO), U3.25 (SWDIO)
UP: SW16.1, U3.28 (GPIO17)
VBUS_SENSE: R5.2, R6.1, U3.36 (GPIO24)
X: SW14.1, U3.32 (GPIO21)
XTAL_IN: C7.2, U3.20 (XTAL_IN), Y1.3
XTAL_OUT: R11.2, U3.21 (XTAL_OUT)
Y: SW10.1, U3.34 (GPIO22)
Z: SW15.1, U3.30 (GPIO19)
~RESET: J2.3 (~RST), R7.2, U3.26 (~RUN)

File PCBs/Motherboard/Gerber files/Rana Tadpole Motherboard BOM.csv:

Designator,Footprint,Quantity,Value,LCSC Part #
"C1, C10, C2, C4",402,4,1uF,C52923
"C11, C12, C13, C14, C15, C16, C17, C3, C5, C6",402,10,100nF,C1525
"C7, C8",402,2,22pF,C1555
C9,402,1,10uF,C15525
D1,D_SOD-123,1,Schottky Diode,C8598
D3,805,1,RED,C84256
"R10, R11",402,2,1k,C11702
R4,402,1,470,C25117
R5,603,1,5.6k,C23189
R6,603,1,10k,C25804
R7,402,1,10k,C25744
"R8, R9",603,2,27,C25190
SW1,SW_SPST_SKQG_WithStem,1,Boot,C318884 
"SW10, SW11, SW12, SW13, SW14, SW15, SW16, SW17, SW18, SW19, SW2, SW20, SW21, SW3, SW4, SW5, SW6, SW7, SW8, SW9",RanaTadpole,20,Kailh GM 4.0,C400254
U1,SOT-23,1,XC6206,C5446
U2,FPC-SMD_X05A26H12G,1,X05A26H12G,C519263
U3,RP2040-QFN-56,1,RP2040,C2040
U4,SOIC-8_5.23x5.23mm_P1.27mm,1,W25Q128JVS,C97521
Y1,Crystal_SMD_3225-4Pin_3.2x2.5mm,1,12MHz,C9002

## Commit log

2023-09-17 Add backplate files
2023-09-17 Update backplate files
2023-10-02 Add design files
2023-10-02 fix typo
2023-10-02 Fix images?
2023-10-02 change POS to CPL in gerber folder filenames
2023-10-02 Add 3D model of backplate
2023-10-12 Fix incorrect bootsel command for gp2040-ce in readme
2025-02-08 Update README.md
    Starting updates to readme, more to come
2025-02-08 Add HayBox-GRAM Tadpole binary
2025-02-19 Add gerbers
2025-02-19 Add kicad files
2025-07-28 Add v2 chassis files
    Includes:
    - chassis STEP file (if getting CNC'd, make a drawing [screenshot with arrows is fine usually if ordering from JLCCNC or similar] to call out M3 tapped holes
    - gasket: separates the motherboard from the backplate. Intended to be die cut from 3mm self adhesive silicone sheet, but can be 3d printed (TPU would work well). Just import into CAD program of your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
    - slide switch cover: self explanatory, panelized for ordering in MJF from JLC.
    - slide switch spacer: intended for FDM, sits in the chassis behind the slide switch cover
